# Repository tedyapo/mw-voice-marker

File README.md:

# mw-voice-marker
SDR synthesized voice frequency marker generator for MW band 

See full project on [hackaday.io](https://hackaday.io/project/21145)

# Installation
I recommend installing the numpy and scipy packages into a python
virtualenv to get newer versions than your distribution may supply.
Here's a recipe you can use for installing all the required dependencies.
Adjust as required for your operating system or distribution.
```
sudo apt-get install python-virtualenv
sudo apt-get install python-pip
sudo apt-get install flite
virtualenv mw-marker-env
source mw-marker-env/bin/activate
pip install numpy scipy
git clone https://github.com/tedyapo/mw-voice-marker
cd mw-voice-marker
wget http://festvox.org/flite/packed/latest/voices/cmu_us_ljm.flitevox
./make_fl2k_file.py > us8192.dat
```
See [the osmocom.org](https://osmocom.org/projects/osmo-fl2k/wiki) wiki for how to install and compile osmo-fl2k.

# Usage
Use the make_fl2k_file.py script to create a data file for use with osmo-fl2k.  The simplest invocation creates a file for the US frequency allocations using an 8192 kHz sampling frequency:
```
fl2k_file -s 8192000 us_order0_8192k.dat
```
You can modify the behavior with command-line options, detailed below.  For example, to create a file with the 9 kHz European channel spacings, you can use:
```
./make_fl2k_file.py eu_order0_8192k.dat -b 531 -e 1602 -s 9 -o 0 -c 4096000 -r 8192000 
```
Here are the command line options:
```
usage: make_fl2k_file.py [-h] [-b BEGIN_FREQ] [-e END_FREQ] [-s FREQ_STEP]
                         [-o ORDER] [-a SCALE] [-c CARRIER_SAMPLE]
                         [-r OUTPUT_SAMPLE]
                         output

create synthesized AM frequency markers for use with osmo-fl2k

positional arguments:
  output                output file

optional arguments:
  -h, --help            show this help message and exit
  -b BEGIN_FREQ, --begin-frequency BEGIN_FREQ
                        first frequency in kHz (default = 530)
  -e END_FREQ, --end-frequency END_FREQ
                        last frequency in kHz (default = 1700)
  -s FREQ_STEP, --spacing FREQ_STEP
                        frequency spacing in kHz (default = 10)
  -o ORDER, --order ORDER
                        sigma-delta modulator order (default = 0)
  -a SCALE, --amplitude-scale SCALE
                        scaling factor for amplitude (default = 1.47)
  -c CARRIER_SAMPLE, --carrier-sample-rate CARRIER_SAMPLE
                        sample rate for carriers (default = 4096000.)
  -r OUTPUT_SAMPLE, --output-sample-rate OUTPUT_SAMPLE
                        output sample rate (default = 65536000.)
 ```
 To play the resulting file, use the fl2k_file command:
 ```
 fl2k_file -s 8192000 us_order0_8192k.dat
 ```
 Don't forget to specify the sampling frequency.  You may not obtain the exact desired sampling frequency.

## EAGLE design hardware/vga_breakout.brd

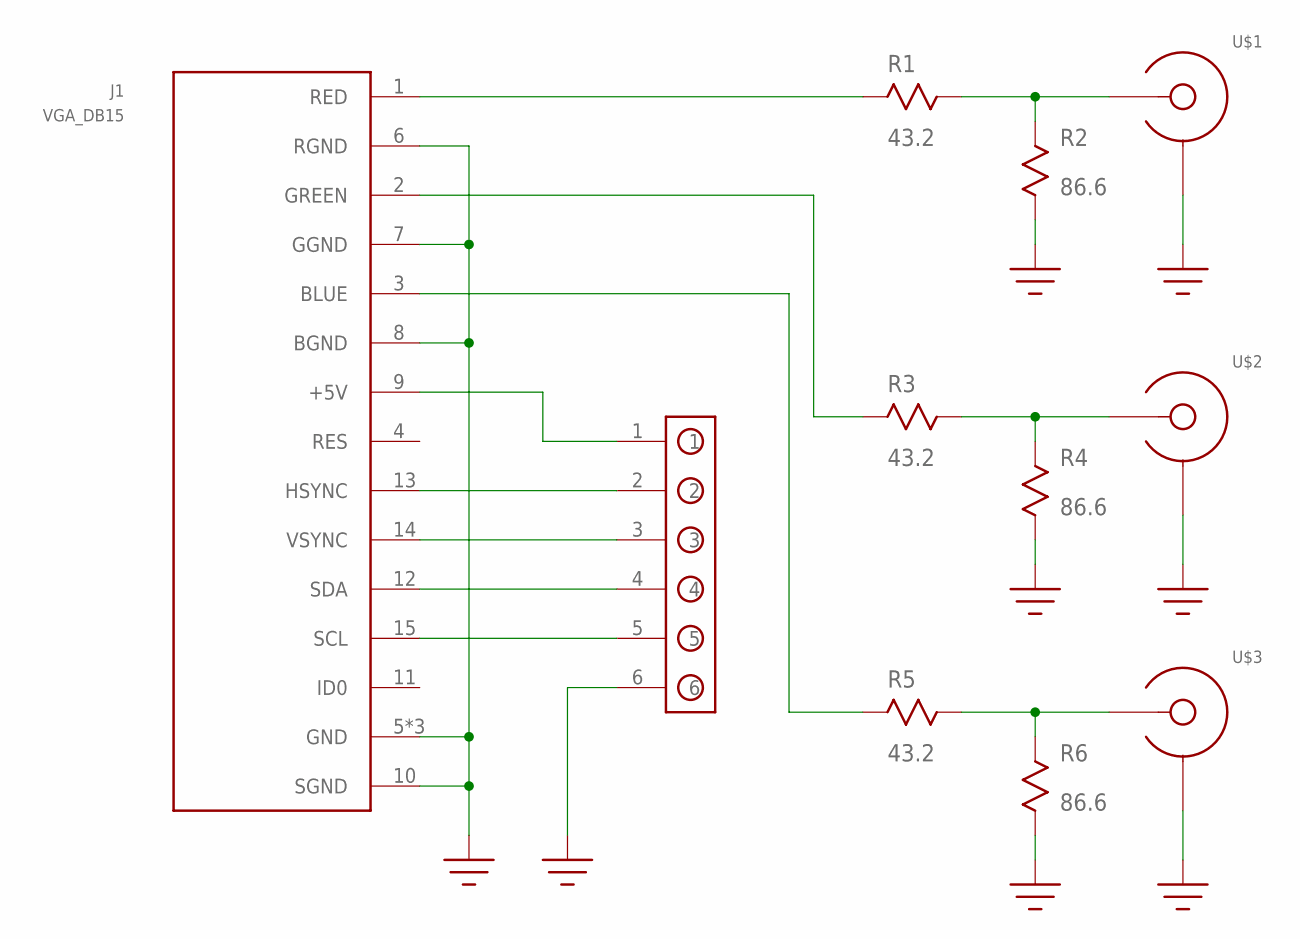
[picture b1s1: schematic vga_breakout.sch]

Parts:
J1: VGA_DB15; VGA_PCB_MALE
R1, R3, R5: 43.2; R0805
R2, R4, R6: 86.6; R0805
U$1, U$2, U$3: EDGE_LAUNCH_JACK; EDGE_LAUNCH_RF_CON
U$9: HEADER_6P

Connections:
+5V: J1.9 (+5V), U$9.1
BLUE: J1.3 (BLUE), R5.P$2
GND: J1.5 (GND), J1.6 (RGND), J1.7 (GGND), J1.8 (BGND), J1.10 (SGND), J1.TAB@1 (GND), J1.TAB@2 (GND), R2.P$2, R4.P$1, R6.P$2, U$1.GND@1 (SHIELD), U$1.GND@2 (SHIELD), U$1.GND@3 (SHIELD), U$1.GND@4 (SHIELD), U$1.GND@5 (SHIELD), U$1.GND@6 (SHIELD), U$1.GND@7 (SHIELD), U$1.GND@8 (SHIELD), U$1.GND@9 (SHIELD), U$1.GND@10 (SHIELD), U$1.GND@11 (SHIELD), U$1.GND@12 (SHIELD), U$1.SHIELD@1 (SHIELD), U$1.SHIELD@2 (SHIELD), U$2.GND@1 (SHIELD), U$2.GND@2 (SHIELD), U$2.GND@3 (SHIELD), U$2.GND@4 (SHIELD), U$2.GND@5 (SHIELD), U$2.GND@6 (SHIELD), U$2.GND@7 (SHIELD), U$2.GND@8 (SHIELD), U$2.GND@9 (SHIELD), U$2.GND@10 (SHIELD), U$2.GND@11 (SHIELD), U$2.GND@12 (SHIELD), U$2.SHIELD@1 (SHIELD), U$2.SHIELD@2 (SHIELD), U$3.GND@1 (SHIELD), U$3.GND@2 (SHIELD), U$3.GND@3 (SHIELD), U$3.GND@4 (SHIELD), U$3.GND@5 (SHIELD), U$3.GND@6 (SHIELD), U$3.GND@7 (SHIELD), U$3.GND@8 (SHIELD), U$3.GND@9 (SHIELD), U$3.GND@10 (SHIELD), U$3.GND@11 (SHIELD), U$3.GND@12 (SHIELD), U$3.SHIELD@1 (SHIELD), U$3.SHIELD@2 (SHIELD), U$9.6
GREEN: J1.2 (GREEN), R3.P$2
HSYNC: J1.13 (HSYNC), U$9.2
unnamed: R5.P$1, R6.P$1, U$3.CENTER
unnamed: R3.P$1, R4.P$2, U$2.CENTER
unnamed: R1.P$2, R2.P$1, U$1.CENTER
RED: J1.1 (RED), R1.P$1
SCL: J1.15 (SCL), U$9.5
SDA: J1.12 (SDA), U$9.4
VSYNC: J1.14 (VSYNC), U$9.3

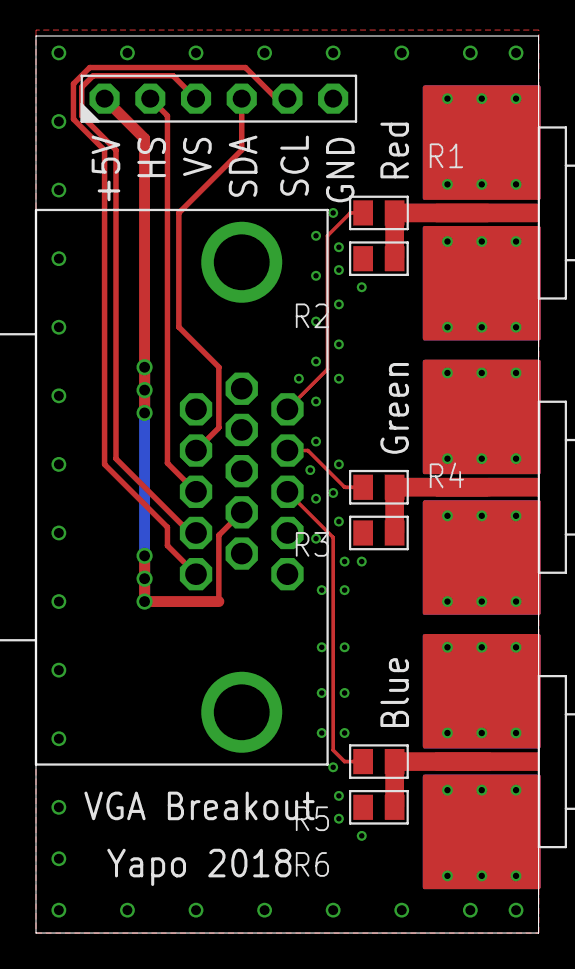
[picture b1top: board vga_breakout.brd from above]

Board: 2 copper layers, 27.9 x 49.8 mm, 11 parts (0 on the bottom side), 12 nets.

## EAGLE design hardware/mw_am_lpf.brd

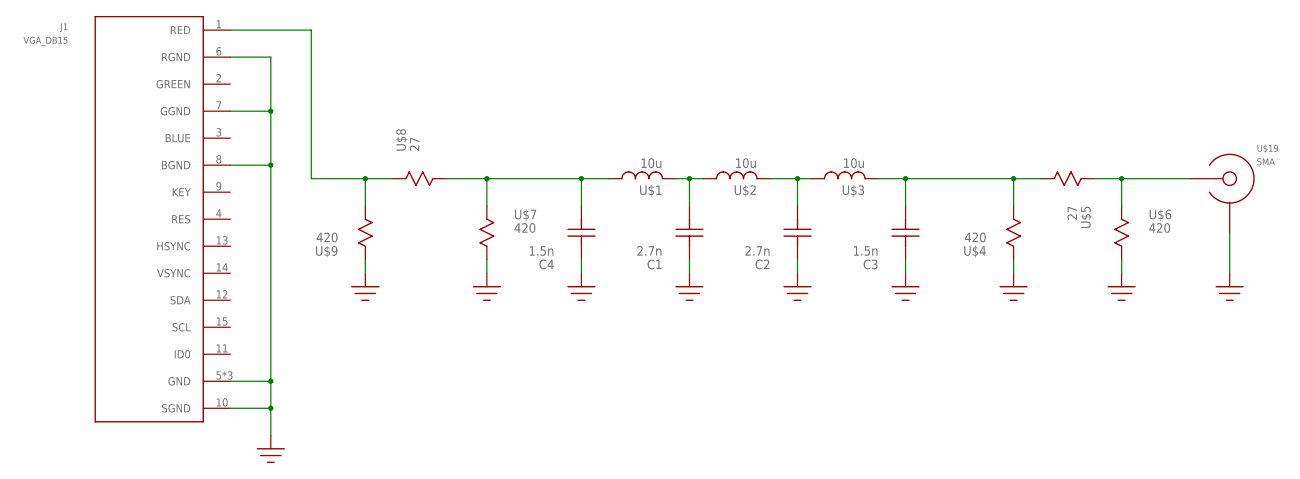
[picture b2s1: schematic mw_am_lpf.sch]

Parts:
C1, C2: 2.7n; 0805
C3, C4: 1.5n; 0805
J1: VGA_DB15; VGA_PCB_MALE
U$1, U$3: 10u; L0.4X0.6
U$2: 10u; L_VERTICAL
U$4, U$6, U$7, U$9: 420; R0805
U$5, U$8: 27; R0805
U$19: SMA; EDGE_LAUNCH_RF_CON

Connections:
GND: C1.P$2, C2.P$2, C3.P$2, C4.P$2, J1.5 (GND), J1.6 (RGND), J1.7 (GGND), J1.8 (BGND), J1.10 (SGND), J1.TAB@1 (GND), J1.TAB@2 (GND), U$4.P$1, U$6.P$2, U$7.P$2, U$9.P$1, U$19.GND@1 (SHIELD), U$19.GND@2 (SHIELD), U$19.GND@3 (SHIELD), U$19.GND@4 (SHIELD), U$19.GND@5 (SHIELD), U$19.GND@6 (SHIELD), U$19.GND@7 (SHIELD), U$19.GND@8 (SHIELD), U$19.GND@9 (SHIELD), U$19.GND@10 (SHIELD), U$19.GND@11 (SHIELD), U$19.GND@12 (SHIELD), U$19.SHIELD@1 (SHIELD), U$19.SHIELD@2 (SHIELD)
unnamed: C2.P$1, U$2.P$2 (2), U$3.P$1 (1)
unnamed: C1.P$1, U$1.P$2 (2), U$2.P$1 (1)
unnamed: C3.P$1, U$3.P$2 (2), U$4.P$2, U$5.P$2
unnamed: C4.P$1, U$1.P$1 (1), U$7.P$1, U$8.P$2
unnamed: U$5.P$1, U$6.P$1, U$19.CENTER
unnamed: J1.1 (RED), U$8.P$1, U$9.P$2

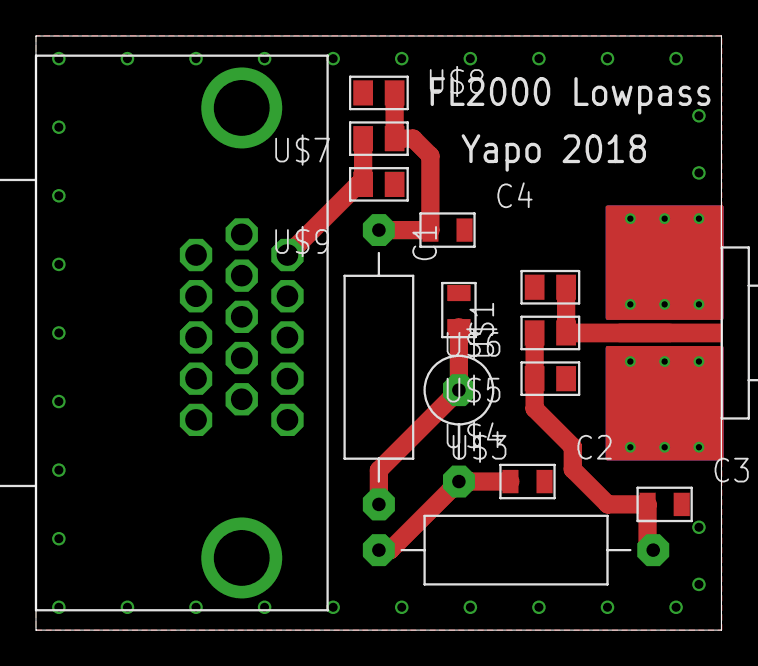
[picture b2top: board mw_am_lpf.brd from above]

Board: 2 copper layers, 38.1 x 33.0 mm, 15 parts (0 on the bottom side), 7 nets.

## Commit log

2017-04-13 cleaned code; exposed explicit parameters
2017-04-13 added proper audio resampling; now using numpy / scipy (much faster)
2017-04-14 added option of generating real baseband samples
2017-04-15 allows quantization to N bits (8, 10, 12, etc)
2018-04-30 added code for fl2k output and pre-generated files for US and EU
2018-05-01 added LPF PCB
2018-05-01 added VGA breakout pcb
2018-05-03 added PTH for VGA connector tabs; LPF has SMA jack
2018-05-04 updated VGA connector footprint
2018-05-04 reduced breakout board to fit in 5cm
2018-05-12 removed soldermask on bottom of SMA connectors
2018-05-13 added coil form design
2018-05-15 added +5V line to breakout PCB
2018-05-15 tented vias on breakout PCB
2018-05-15 updated gerbers missed in last commit
